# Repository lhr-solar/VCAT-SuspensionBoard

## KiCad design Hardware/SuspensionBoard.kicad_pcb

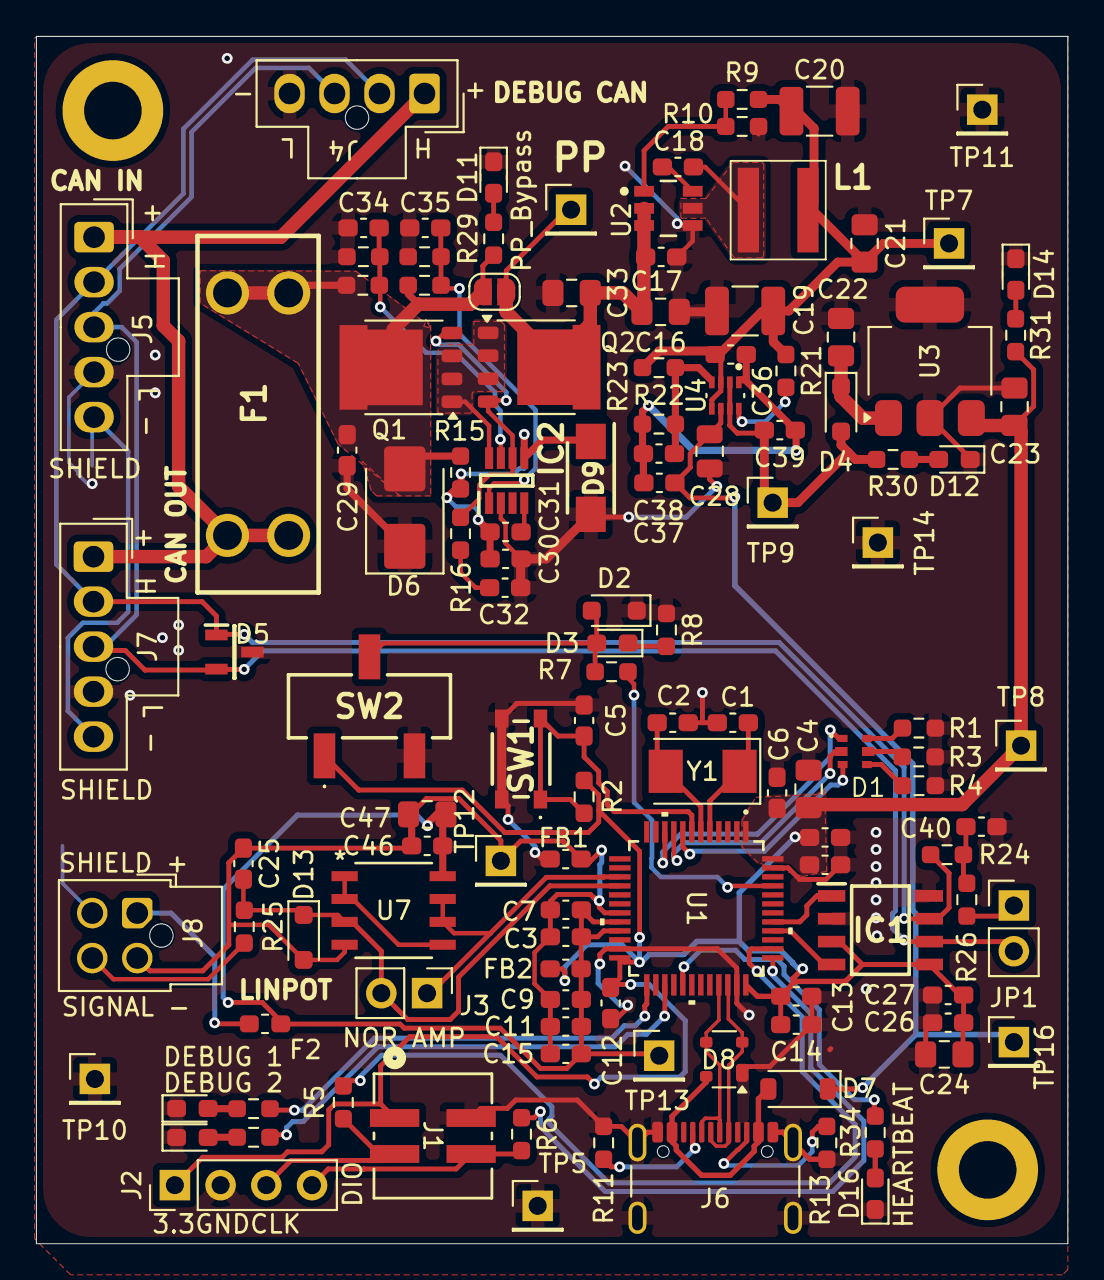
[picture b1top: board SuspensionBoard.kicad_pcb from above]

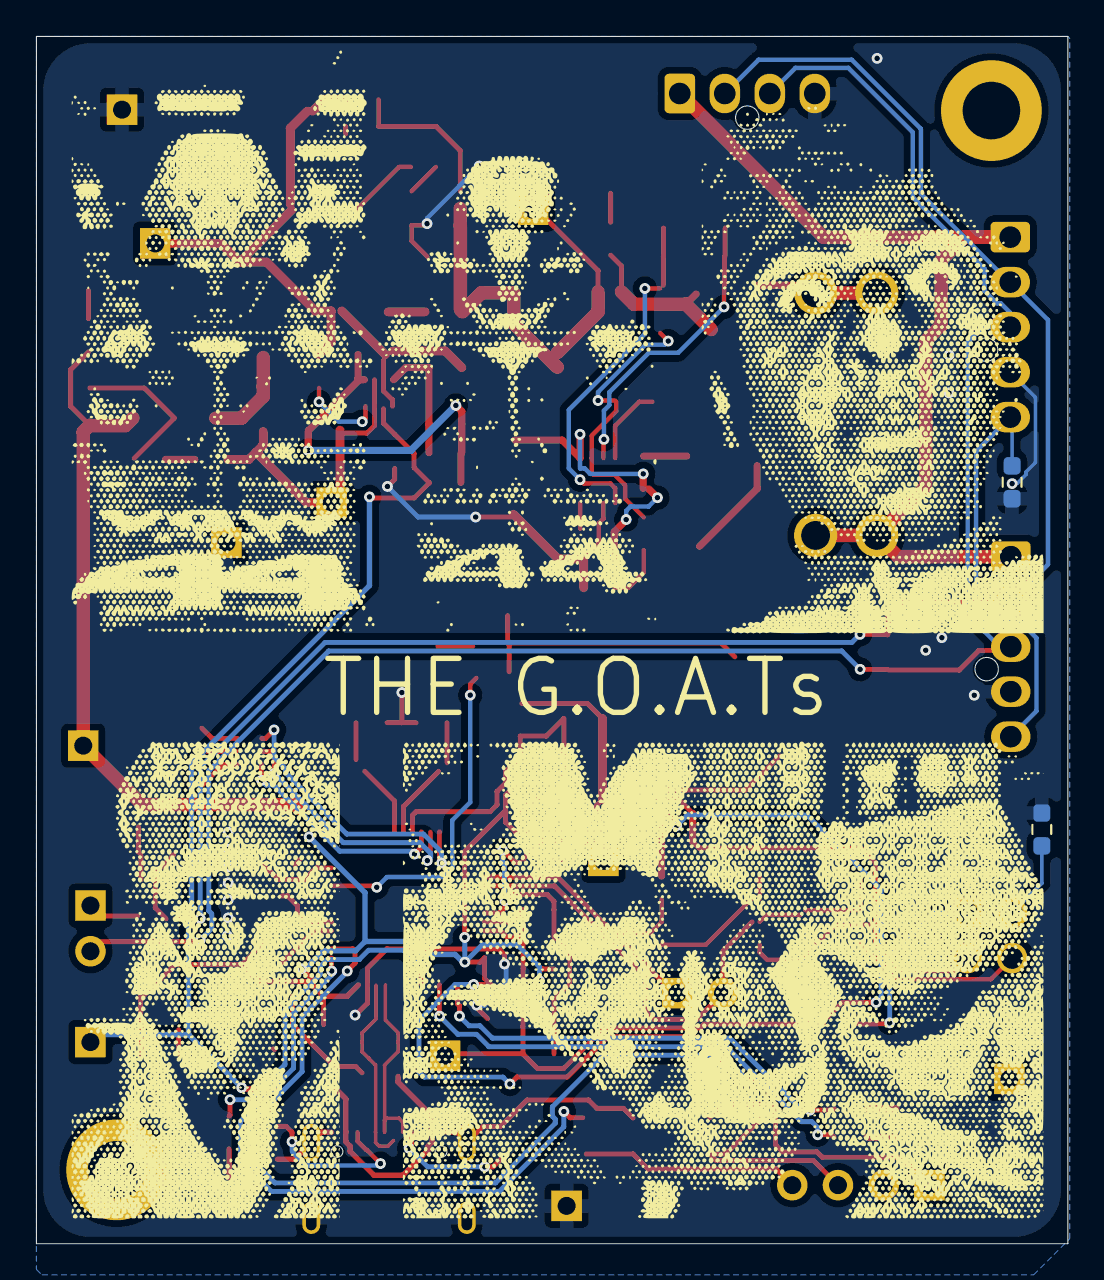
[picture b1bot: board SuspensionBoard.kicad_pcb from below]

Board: 2 copper layers, 57.3 x 67.1 mm, 128 parts (2 on the bottom side), 67 nets.

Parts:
C1, C2: 26p; C_0603_1608Metric_Pad1.08x0.95mm_HandSolder
C3, C5, C6, C7, C8, C10, C12, C13, C14, C26, C27, C29, C34, C35, C36, C37, C38, C39, C40: 0.1u; C_0603_1608Metric_Pad1.08x0.95mm_HandSolder
C4, C22, C23, C24, C33, C47: 10u; C_0805_2012Metric_Pad1.18x1.45mm_HandSolder
C9, C11, C25, C30: 1u; C_0603_1608Metric_Pad1.08x0.95mm_HandSolder
C15, C17, C18, C46: 100n; C_0603_1608Metric_Pad1.08x0.95mm_HandSolder
C16: 4.7u; C_0805_2012Metric_Pad1.18x1.45mm_HandSolder
C19, C20: 22u; C_1210_3225Metric_Pad1.33x2.70mm_HandSolder
C21: 3.3u; C_0805_2012Metric_Pad1.18x1.45mm_HandSolder
C28: 10u; C_0805_2012Metric
C31: 220n; C_0603_1608Metric_Pad1.08x0.95mm_HandSolder
C32: 10n; C_0603_1608Metric_Pad1.08x0.95mm_HandSolder
D1: RGB_LED
D2, D13: TVS; D_SOD-323_HandSoldering
D3, D15, D16: LED; LED_0603_1608Metric_Pad1.05x0.95mm_HandSolder
D4: SBA130CH-AU_R1_000A1; D_SOD-323_HandSoldering
D5: CDSOT23-T24CAN
D6: SMBJ15CA; D_SMB
D7: D_Schottky; D_SOD-123
D8: SP0503BAHT; SOT-143
D9: SMAF4758A; SODFL5026X125N
D11: 12VIN_LED; LED_0603_1608Metric_Pad1.05x0.95mm_HandSolder
D12: 5V_LED; LED_0603_1608Metric_Pad1.05x0.95mm_HandSolder
D14: 3.3V_LED; LED_0603_1608Metric_Pad1.05x0.95mm_HandSolder
D17: HB; LED_0603_1608Metric_Pad1.05x0.95mm_HandSolder
F1: Fuse; Fuse-3557-2
F2: Polyfuse; Fuse_0603_1608Metric_Pad1.05x0.95mm_HandSolder
FB1, FB2: FerriteBead; C_0603_1608Metric_Pad1.08x0.95mm_HandSolder
IC1: TCAN3413DR
IC2: LM74502DDFR
J1: SWD_Header; SWD_Conn
J2: SWD; PinHeader_1x04_P2.54mm_Vertical
J3: Conn_01x02; PinHeader_1x02_P2.54mm_Vertical
J4: CAN_DEBUG_NANO_01x04; Molex_Nano-Fit_105309-xx04_1x04_P2.50mm_Vertical
J5: CAN_IN; Molex_Nano-Fit_105309-xx05_1x05_P2.50mm_Vertical
J6: USB_C_Receptacle_USB2.0_16P; USB_C_Receptacle_GCT_USB4105-xx-A_16P_TopMnt_Horizontal
J7: CAN_OUT; Molex_Nano-Fit_105309-xx05_1x05_P2.50mm_Vertical
J8: Conn_02x02_Counter_Clockwise; Molex_Nano-Fit_105310-xx04_2x02_P2.50mm_Vertical
JP1: TRM; PinHeader_1x02_P2.54mm_Vertical
JP2: PP_Bypass; SolderJumper-2_P1.3mm_Open_RoundedPad1.0x1.5mm
L1: 8.2u; XAL5050822MEC
Q1, Q2: PSMN012-100YS; LFPAK56
R1, R3, R4, R8, R27, R28, R34: 1k; R_0603_1608Metric_Pad0.98x0.95mm_HandSolder
R2, R7, R15, R21: 10k; R_0603_1608Metric_Pad0.98x0.95mm_HandSolder
R5, R6: 22; R_0603_1608Metric_Pad0.98x0.95mm_HandSolder
R9, R17, R19: 100k; R_0603_1608Metric_Pad0.98x0.95mm_HandSolder
R10: 19.1k; R_0603_1608Metric_Pad0.98x0.95mm_HandSolder
R11, R13: 5.1k; R_0603_1608Metric_Pad0.98x0.95mm_HandSolder
R12, R32: 0; R_0603_1608Metric_Pad0.98x0.95mm_HandSolder
R16: 33; R_0603_1608Metric_Pad0.98x0.95mm_HandSolder
R18: 7.32k; R_0603_1608Metric_Pad0.98x0.95mm_HandSolder
R20: 15.8k; R_0603_1608Metric_Pad0.98x0.95mm_HandSolder
R22: 16k; R_0603_1608Metric_Pad0.98x0.95mm_HandSolder
R23, R25: 4.7k; R_0603_1608Metric_Pad0.98x0.95mm_HandSolder
R24, R26: 60; R_0603_1608Metric_Pad0.98x0.95mm_HandSolder
R29: 5k; R_0603_1608Metric_Pad0.98x0.95mm_HandSolder
R30: 2k; R_0603_1608Metric_Pad0.98x0.95mm_HandSolder
R31: 250; R_0603_1608Metric_Pad0.98x0.95mm_HandSolder
SW1: Reset; TL3365AF180QG
SW2: SW_SPDT; BootSW
TP5: GND_Point_0; PinHeader_1x01_P2.54mm_Vertical
TP7: BUCK_5V_TP; PinHeader_1x01_P2.54mm_Vertical
TP8: 3.3V_Point; PinHeader_1x01_P2.54mm_Vertical
TP9: 5V_Point; PinHeader_1x01_P2.54mm_Vertical
TP10: GND_Point_1; PinHeader_1x01_P2.54mm_Vertical
TP11: GND_Point_2; PinHeader_1x01_P2.54mm_Vertical
TP12: GNDA_POINT; PinHeader_1x01_P2.54mm_Vertical
TP13: 3.3VA_POINT; PinHeader_1x01_P2.54mm_Vertical
TP14: GND_POINT; PinHeader_1x01_P2.54mm_Vertical
TP15: 12V_Point; PinHeader_1x01_P2.54mm_Vertical
TP16: USB_5V_TP; PinHeader_1x01_P2.54mm_Vertical
U1: STM32G473CETx; 48PinMCU
U2: LMR51635XDDCR; DDC0006A-MFG
U3: MCP1826S; SOT-223-3_TabPin2
U4: TPS2117DRLR
U7: Opamp_Dual; SOIC8_D_TEX
Y1: Crystal; Crystal_SMD_Abracon_ABM3-2Pin_5.0x3.2mm

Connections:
+3.3V: C4.1, C6.1, C8.1, C10.1, C12.1, C13.1, C14.1, C23.2, C24.1, C26.1, C27.1, FB2.1, IC1.3 (VCC), IC1.5 (SHDNV_IO), J1.1, J2.1, R2.2, R31.1, SW2.1 (A), TP8.1 (1_1), U1.1 (VBAT), U1.24 (VDD), U1.36 (VDD), U1.48 (VDD), U3.3 (VO)
+3.3VA: C3.1, C7.1, C9.1, C11.1, C15.1, C46.2, C47.2, F2.1, FB2.2, TP13.1 (1_1), U1.20 (VREF+), U1.21 (VDDA), U7.8 (V+)
+12Vin: F1.2, J4.1 (12V), J5.1 (12V), J7.1 (12V)
/CAN_H: D5.1 (CAN_H), IC1.7 (CANH), J4.2 (CAN_H), J5.2 (CAN_H), J7.2 (CAN_H), R24.1
/CAN_L: D5.2 (CAN_L), IC1.6 (CANL), J4.3 (CAN_L), J5.3 (CAN_L), J7.3 (CAN_L), JP1.2 (B)
/CAN_Transceiver/CAN_RX: IC1.4 (RXD), U1.40 (PB3)
/CAN_Transceiver/CAN_TX: IC1.1 (TXD), U1.41 (PB4)
/LINPOT_SIGNAL: J8.3, R25.2
/LinPot/AMP_LinPot: J3.1, U1.15 (PA7), U7.6 (-), U7.7
/LinPot/LinPot_Output: C25.1, D13.1 (A1), J3.2, R25.1, U1.16 (PB0), U7.3 (+)
/MCU+USB/48PinMCU/BOOT0: R7.1, U1.45 (PB8-BOOT0)
/MCU+USB/48PinMCU/NRST: C5.1, R2.1, SW1.1, U1.7 (PG10-NRST)
/MCU+USB/48PinMCU/PA0: D1.5, U1.8 (PA0-GPIO_BLUE)
/MCU+USB/48PinMCU/PA1: D1.3, U1.9 (PA1_GPIO_RED)
/MCU+USB/48PinMCU/PA2: D1.1, U1.10 (PA2-GPIO_GREEN)
/MCU+USB/48PinMCU/PB11: R28.1, U1.25 (PB11)
/MCU+USB/48PinMCU/PB13: R27.1, U1.27 (PB13)
/MCU+USB/48PinMCU/PB15: R34.1, U1.29 (PB15)
/MCU+USB/48PinMCU/SWCLK: R5.1, U1.38 (PA14)
/MCU+USB/48PinMCU/SWDIO: R6.1, U1.37 (PA13)
/MCU+USB/48PinMCU/USB_DN: D8.3 (K), J6.A7 (D-), J6.B7 (D-), U1.33 (PA11)
/MCU+USB/48PinMCU/USB_DP: D8.2 (K), J6.A6 (D+), J6.B6 (D+), U1.34 (PA12)
/MCU+USB/USB-C_Connector/CC1: J6.A5 (CC1), R11.2
/MCU+USB/USB-C_Connector/CC2: J6.B5 (CC2), R13.2
/MCU+USB/USB-C_Connector/VBUS_IN: D7.2 (A), D8.4 (K), J6.A4 (VBUS), J6.A9 (VBUS), J6.B4 (VBUS), J6.B9 (VBUS)
/PWR_LINPOT: F2.2, J8.1
/Power_Rail/5V_BUCK: C19.1, C20.1, C21.1, C36.1, L1.2, R9.1, R21.1, R22.1, TP7.1 (1_1), U4.3 (VIN1), U4.5 (MODE)
/Power_Rail/5V_MUX: C39.1, D4.2 (A), R30.1, TP9.1 (1_1), U4.2 (VOUT), U4.7 (VOUT__1)
/Power_Rail/12VBuck/CB: C18.1, U2.6 (CB)
/Power_Rail/12VBuck/FB: R9.2, R10.1, U2.1 (FB)
/Power_Rail/12VBuck/SW: C18.2, L1.1, U2.5 (SW)
/Power_Rail/12V_FUSED: C29.1, D6.2 (A2), F1.1, JP2.1 (A), Q1.5, R15.2, R17.1, R19.1, R29.1
/Power_Rail/+12v_PP: C16.1, C17.1, C33.1, JP2.2 (B), Q2.5, TP15.1 (1_1), U2.2 (EN), U2.3 (VIN)
/Power_Rail/PowerProtection/EN/UVLO: C35.1, IC2.1 (EN/UVLO), R19.2, R20.2
/Power_Rail/PowerProtection/OV: C34.1, IC2.7 (OV), R17.2, R18.1
/Power_Rail/PowerProtection/gate: IC2.6 (GATE), Q1.4, Q2.4, R16.2
/Power_Rail/PowerProtection/source: IC2.8 (SRC), Q1.1, Q1.2, Q1.3, Q2.1, Q2.2, Q2.3
/Power_Rail/Power_Mux/MX_GND: C36.2, C37.2, C38.2, C39.2, R23.2, U4.1 (GND)
/Power_Rail/Power_Mux/PR1: C38.1, R22.2, R23.1, U4.4 (PR1)
/Shield: J5.5 (SHIELD), J7.5 (SHIELD), R32.2
/USB_5V: C28.2, C37.1, D7.1 (K), TP16.1 (1_1), U4.6 (VIN2)
GND: C1.1, C2.2, C4.2, C5.2, C6.2, C8.2, C10.2, C12.2, C13.2, C14.2, C16.2, C17.2, C19.2, C20.2, C21.2, C22.1, C23.1, C24.2, C26.2, C27.2, C28.1, C29.2, C30.1, C32.2, C33.2, C34.2, C35.2, C40.1, D2.1 (A1), D5.3 (GND), D6.1 (A1), D8.1 (A), D9.2 (A), D11.1 (K), D12.1 (K), D14.1 (K), D15.1 (K), D16.1 (K), D17.1 (K), FB1.2, IC1.2 (GND), IC1.8 (STB), IC2.2 (GND), J1.2, J2.2, J4.4 (GND), J5.4 (GND), J6.A1 (GND), J6.A12 (GND), J6.B1 (GND), J6.B12 (GND), J6.S1 (SHIELD), J6.S2 (Shield), J6.S3 (Shield), J6.S4 (Shield), J7.4 (GND), R1.2, R3.2, R4.2, R8.2, R10.2, R11.1, R12.2, R13.1, R18.2, R20.1, R32.1, SW1.2, SW2.3 (C), TP5.1 (1_1), TP10.1 (1_1), TP11.1 (1_1), TP14.1 (1_1), U1.23 (VSS), U1.35 (VSS), U1.47 (VSS), U2.4 (GND), U3.2 (GND)
GNDA: C3.2, C7.2, C9.2, C11.2, C15.2, C25.2, C46.1, C47.1, D13.2 (A2), FB1.1, J8.2, TP12.1 (1_1), U1.19 (VSSA), U7.4 (V-)
unnamed: C32.1, R16.1
unnamed: C40.2, R24.2, R26.1
unnamed: D1.2, R1.1
unnamed: D1.4, R3.1
unnamed: D1.6, R4.1
unnamed: D2.2 (A2), D3.2 (A), R7.2, SW2.2 (B)
unnamed: D3.1 (K), R8.1
unnamed: C22.2, D4.1 (K), U3.1 (VI)
unnamed: C30.2, C31.1, D9.1 (K), IC2.5 (VS), R15.1
unnamed: D11.2 (A), R29.2
unnamed: D12.2 (A), R30.2
unnamed: D14.2 (A), R31.2
unnamed: D15.2 (A), R27.2
unnamed: D16.2 (A), R34.2
unnamed: D17.2 (A), R28.2
unnamed: C31.2, IC2.4 (VCAP)
unnamed: J1.3, J2.3, R5.2
unnamed: J1.4, J2.4, R6.2
unnamed: J8.4, R12.1
unnamed: JP1.1 (A), R26.2
unnamed: C1.2, U1.5 (PF0-OSC_IN), Y1.1
unnamed: C2.1, U1.6 (PF1-OSC_OUT), Y1.2
unnamed: R21.2, U4.8 (ST)
unnamed: U7.1, U7.2 (-), U7.5 (+)

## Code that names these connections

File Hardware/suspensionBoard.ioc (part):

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Mcu.Name=STM32G473C(B-C-E)Tx
Mcu.Package=LQFP48
Mcu.UserName=STM32G473CETx
PA11.Mode=Device
PA11.Signal=USB_DM
PA12.Mode=Device
PA12.Signal=USB_DP
PA3.Mode=IN4-Single-Ended
PA3.Signal=ADC1_IN4
PB11.Signal=GPIO_Output
PB13.Signal=GPIO_Output
PB14.Mode=IN5-Single-Ended
PB14.Signal=ADC1_IN5
PB15.Signal=GPIO_Output
PB3.Mode=FDCAN_Activate
PB3.Signal=FDCAN3_RX
PB4.Mode=FDCAN_Activate
PB4.Signal=FDCAN3_TX
RCC.HSE_VALUE=8000000
RCC.SYSCLKFreq_VALUE=16000000
board=custom
